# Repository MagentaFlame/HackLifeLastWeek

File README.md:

Helloooo this is last week of design for hack life, and I'm doing a split keyboard!
Ever since I learned about being able to do one from Hack club, I've been looking for opportunities to. Now that I got one, hopefully I have enough free time to do it. I feel bad about not doing my college apps and my tons of hw...

Schematic!

The labels are kind of scuffed. I pretty much made a matrix of 25 keys, using as much as possible, and customized where the pins pointed to so it was easier to route on the pcb. 

PCB!

This took so so long. So currently, most of the letter keys are assembled in a staggered format, similar to a regular keyboard. This is to retain muscle memory for typing and gaming. The ctrl button the left side and space button on the right are still within the 5x5 matrix for the pins, but are one row down for muscle memory.

Code!

I had to create a custom keyboard module using zmk. I learned and implemented making new shields for each side, setting ids, doing soft-off power management, and doing keymaps. In the keymaps, mod-morphs, macros, hold-taps, and regular kps were used to give more complex, unique functionalities. This way, it isn't one/two outputs for each press, but potentially 3/4 depending on which layer (gaming or default) is toggled and the combination of keys pressed. 
I also made sure to write my configs down for future reference and to make sure I don't forget over the few days I do this project.

CAD!

Okay so I wanted the two sides to be vastly different - one hard and modern, while the other more flowy. But, the flowy side isn't to my liking as much as the geometric side b/c I didn't make it flowy enough lol. Anyways, hopefully the color combos will be good. I add only engravings this time, b/c extra details like changing wall geometry and embossing will take time I don't have unfortunately.
The pictures show the colors for the cases. The keycaps for the purple side will be gray and more jagged than the red keycaps on the orange side.
https://cad.onshape.com/documents/0349a2efe14c8a7447e63041/w/2e8c132947c776d3aa7bf3c9/e/34fe7648d6cb8c38b9c40c14 

BOM!

| Item | Qty |	Supplier | Cost/item |	Total Cost |	link |
| ---- | --- |  -------- | --------- | ----------- | ----- |
|Lipo batteries 2pc	|1|	Aliexpress|	$6.39|	$6.39|	https://www.aliexpress.us/item/3256813194775738.html?spm=a2g0o.cart.0.0.3b7f38dawnxLUB&mp=1&pdp_npi=6%40dis%21USD%21USD+17.06%21USD+6.39%21%21USD+5.38%21%21%21%4021032c8d17939128056472314e101d%2112000060946039596%21ct%21US%218326311333%21%212%210%21&_gl=1*vcxzl1*_gcl_aw*R0NMLjE3OTM4MjU2ODEuQ2p3S0NBanc5UHZXQmhBeEVpd0FkZHpZeWZ0RWJBRHV0MFp1THBmbjhScHQ0RHNHWnd5N2dsNnZkbnFycTN0ZDZIZUFDYklOaW9WZ2dCb0MxZ3NRQXZEX0J3RQ..*_gcl_dc*R0NMLjE3OTM4MjU2ODEuQ2p3S0NBanc5UHZXQmhBeEVpd0FkZHpZeWZ0RWJBRHV0MFp1THBmbjhScHQ0RHNHWnd5N2dsNnZkbnFycTN0ZDZIZUFDYklOaW9WZ2dCb0MxZ3NRQXZEX0J3RQ..*_gcl_au*MTczOTE2ODQ4MC4xNzkyMTg4MzIz*_ga*MTU3NzE5MTE5Ny4xNzkzMjI3OTEx*_ga_VED1YSGNC7*czE3OTM5MDgwNzIkbzckZzEkdDE3OTM5MTI4MjQkajQwJGwwJGgw&gatewayAdapt=glo2usa |
|Hot swap sockets|	1|Aliexpress|	$5.43|	$5.43|	https://www.aliexpress.us/item/2251832764937566.html?spm=a2g0o.cart.0.0.3b7f38da0QjVnx&mp=1&pdp_npi=6%40dis%21USD%21USD+6.06%21USD+5.43%21%21USD+4.65%21%21%21%4021030f4a17939133456333682e0f45%2112000036652544705%21ct%21US%218326311333%21%211%210%21&_gl=1*f2u40p*_gcl_aw*R0NMLjE3OTM4MjU2ODEuQ2p3S0NBanc5UHZXQmhBeEVpd0FkZHpZeWZ0RWJBRHV0MFp1THBmbjhScHQ0RHNHWnd5N2dsNnZkbnFycTN0ZDZIZUFDYklOaW9WZ2dCb0MxZ3NRQXZEX0J3RQ..*_gcl_dc*R0NMLjE3OTM4MjU2ODEuQ2p3S0NBanc5UHZXQmhBeEVpd0FkZHpZeWZ0RWJBRHV0MFp1THBmbjhScHQ0RHNHWnd5N2dsNnZkbnFycTN0ZDZIZUFDYklOaW9WZ2dCb0MxZ3NRQXZEX0J3RQ..*_gcl_au*MTczOTE2ODQ4MC4xNzkyMTg4MzIz*_ga*MTU3NzE5MTE5Ny4xNzkzMjI3OTEx*_ga_VED1YSGNC7*czE3OTM5MDgwNzIkbzckZzEkdDE3OTM5MTMzNDckajU4JGwwJGgw&gatewayAdapt=glo2usa|
|2M Resistor (100pc)|	1|	Aliexpress|	$1.86	|$1.86	|https://www.aliexpress.us/item/3256806797741926.html?spm=a2g0o.cart.0.0.3b7f38da0QjVnx&mp=1&pdp_npi=6%40dis%21USD%21USD%202.82%21USD%201.86%21%21USD%201.59%21%21%21%4021030f4a17939133456333682e0f45%2112000038943042510%21ct%21US%218326311333%21%211%210%21&_gl=1*hvxv5j*_gcl_aw*R0NMLjE3OTM4MjU2ODEuQ2p3S0NBanc5UHZXQmhBeEVpd0FkZHpZeWZ0RWJBRHV0MFp1THBmbjhScHQ0RHNHWnd5N2dsNnZkbnFycTN0ZDZIZUFDYklOaW9WZ2dCb0MxZ3NRQXZEX0J3RQ..*_gcl_dc*R0NMLjE3OTM4MjU2ODEuQ2p3S0NBanc5UHZXQmhBeEVpd0FkZHpZeWZ0RWJBRHV0MFp1THBmbjhScHQ0RHNHWnd5N2dsNnZkbnFycTN0ZDZIZUFDYklOaW9WZ2dCb0MxZ3NRQXZEX0J3RQ..*_gcl_au*MTczOTE2ODQ4MC4xNzkyMTg4MzIz*_ga*MTU3NzE5MTE5Ny4xNzkzMjI3OTEx*_ga_VED1YSGNC7*czE3OTM5MDgwNzIkbzckZzEkdDE3OTM5MTMzNjIkajQzJGwwJGgw&gatewayAdapt=glo2usa&_randl_shipto=US|
|806k Resistor (100pc)	|1|	Aliexpress|	$2.28|	$2.28|	https://www.aliexpress.us/item/3256804997915352.html?spm=a2g0o.cart.0.0.3b7f38da0QjVnx&mp=1&pdp_npi=6%40dis%21USD%21USD+2.28%21USD+2.28%21%21USD+1.95%21%21%21%4021030f4a17939133456333682e0f45%2112000032017018120%21ct%21US%218326311333%21%211%210%21&_gl=1*10htlic*_gcl_aw*R0NMLjE3OTM4MjU2ODEuQ2p3S0NBanc5UHZXQmhBeEVpd0FkZHpZeWZ0RWJBRHV0MFp1THBmbjhScHQ0RHNHWnd5N2dsNnZkbnFycTN0ZDZIZUFDYklOaW9WZ2dCb0MxZ3NRQXZEX0J3RQ..*_gcl_dc*R0NMLjE3OTM4MjU2ODEuQ2p3S0NBanc5UHZXQmhBeEVpd0FkZHpZeWZ0RWJBRHV0MFp1THBmbjhScHQ0RHNHWnd5N2dsNnZkbnFycTN0ZDZIZUFDYklOaW9WZ2dCb0MxZ3NRQXZEX0J3RQ..*_gcl_au*MTczOTE2ODQ4MC4xNzkyMTg4MzIz*_ga*MTU3NzE5MTE5Ny4xNzkzMjI3OTEx*_ga_VED1YSGNC7*czE3OTM5MDgwNzIkbzckZzEkdDE3OTM5MTM0NTEkajU4JGwwJGgw&gatewayAdapt=glo2usa|
|1N5819 diode (100pc)|	1|	Aliexpress|	$2.52|	$2.52|	https://aliexpress.us/item/3256811563559109.html?spm=a2g0o.cart.0.0.3b7f38da0QjVnx&mp=1&pdp_npi=6%40dis%21USD%21USD%202.71%21USD%202.52%21%21USD%202.16%21%21%21%4021030f4a17939133456333682e0f45%2112000056430529218%21ct%21US%218326311333%21%211%210%21&_gl=1*p639if*_gcl_aw*R0NMLjE3OTM4MjU2ODEuQ2p3S0NBanc5UHZXQmhBeEVpd0FkZHpZeWZ0RWJBRHV0MFp1THBmbjhScHQ0RHNHWnd5N2dsNnZkbnFycTN0ZDZIZUFDYklOaW9WZ2dCb0MxZ3NRQXZEX0J3RQ..*_gcl_dc*R0NMLjE3OTM4MjU2ODEuQ2p3S0NBanc5UHZXQmhBeEVpd0FkZHpZeWZ0RWJBRHV0MFp1THBmbjhScHQ0RHNHWnd5N2dsNnZkbnFycTN0ZDZIZUFDYklOaW9WZ2dCb0MxZ3NRQXZEX0J3RQ..*_gcl_au*MTczOTE2ODQ4MC4xNzkyMTg4MzIz*_ga*MTU3NzE5MTE5Ny4xNzkzMjI3OTEx*_ga_VED1YSGNC7*czE3OTM5MDgwNzIkbzckZzEkdDE3OTM5MTM1MDckajIkbDAkaDA.&gatewayAdapt=glo2usa&_randl_shipto=US|
|Outemu Silent Lemon v3 Switch (50pc)|	1|	Aliexpress|	$9.49|	$9.49|	https://www.aliexpress.us/item/3256806837508228.html?spm=a2g0o.cart.0.0.3b7f38da0QjVnx&mp=1&pdp_npi=6%40dis%21USD%21USD+10.66%21USD+9.49%21%21USD+8.12%21%21%21%4021030f4a17939133456333682e0f45%2112000039119542623%21ct%21US%218326311333%21%211%210%21&_gl=1*xwxxe5*_gcl_aw*R0NMLjE3OTM4MjU2ODEuQ2p3S0NBanc5UHZXQmhBeEVpd0FkZHpZeWZ0RWJBRHV0MFp1THBmbjhScHQ0RHNHWnd5N2dsNnZkbnFycTN0ZDZIZUFDYklOaW9WZ2dCb0MxZ3NRQXZEX0J3RQ..*_gcl_dc*R0NMLjE3OTM4MjU2ODEuQ2p3S0NBanc5UHZXQmhBeEVpd0FkZHpZeWZ0RWJBRHV0MFp1THBmbjhScHQ0RHNHWnd5N2dsNnZkbnFycTN0ZDZIZUFDYklOaW9WZ2dCb0MxZ3NRQXZEX0J3RQ..*_gcl_au*MTczOTE2ODQ4MC4xNzkyMTg4MzIz*_ga*MTU3NzE5MTE5Ny4xNzkzMjI3OTEx*_ga_VED1YSGNC7*czE3OTM5MDgwNzIkbzckZzEkdDE3OTM5MTM1MTYkajYwJGwwJGgw&gatewayAdapt=glo2usa|
|XIAO nRF52840|	2|	Seeed Studio|	$9.99|	$19.98	|https://www.seeedstudio.com/Seeed-XIAO-BLE-nRF52840-p-5201.html?srsltid=AYCX9vLI_KwrC99kiBzCmS7TrKkTqYekleFYA7gHI7japWQgcSidnN09|
|Custom pcb|	1|	JLCPCB|	$16.95|	$16.95|	https://cart.jlcpcb.com/shopcart/cart/|
|M2 screws 6mm (200pc)|	1|	Aliexpress|	$2.43|	$2.43|	https://aliexpress.us/item/3256808326585307.html?spm=a2g0o.cart.0.0.3a3d38daXM6BNr&mp=1&pdp_npi=6%40dis%21USD%21USD%203.00%21USD%202.43%21%21USD%202.10%21%21%21%40210303cd17939214157478397e0ddd%2112000045495593376%21ct%21US%218326311333%21%211%210%21&_gl=1*i5d2vl*_gcl_aw*R0NMLjE3OTM4MjU2ODEuQ2p3S0NBanc5UHZXQmhBeEVpd0FkZHpZeWZ0RWJBRHV0MFp1THBmbjhScHQ0RHNHWnd5N2dsNnZkbnFycTN0ZDZIZUFDYklOaW9WZ2dCb0MxZ3NRQXZEX0J3RQ..*_gcl_dc*R0NMLjE3OTM4MjU2ODEuQ2p3S0NBanc5UHZXQmhBeEVpd0FkZHpZeWZ0RWJBRHV0MFp1THBmbjhScHQ0RHNHWnd5N2dsNnZkbnFycTN0ZDZIZUFDYklOaW9WZ2dCb0MxZ3NRQXZEX0J3RQ..*_gcl_au*MTczOTE2ODQ4MC4xNzkyMTg4MzIz*_ga*MTU3NzE5MTE5Ny4xNzkzMjI3OTEx*_ga_VED1YSGNC7*czE3OTM5MjEwODgkbzgkZzEkdDE3OTM5MjE0MTYkajU0JGwwJGgw&gatewayAdapt=glo2usa&_randl_shipto=US|
|Estimated total shipping|	1|			$11.10|

Only after making the hardware did I realized just how much it costs, even with Aliexpress and the 11.11 deals (hopefully I can get this approved by then). The microcontrollers and custom pcb cost the most, but that is to be expected. Just once added together, it accumulated to a lot. I think I can get enough hours for the tier 3 funding though.

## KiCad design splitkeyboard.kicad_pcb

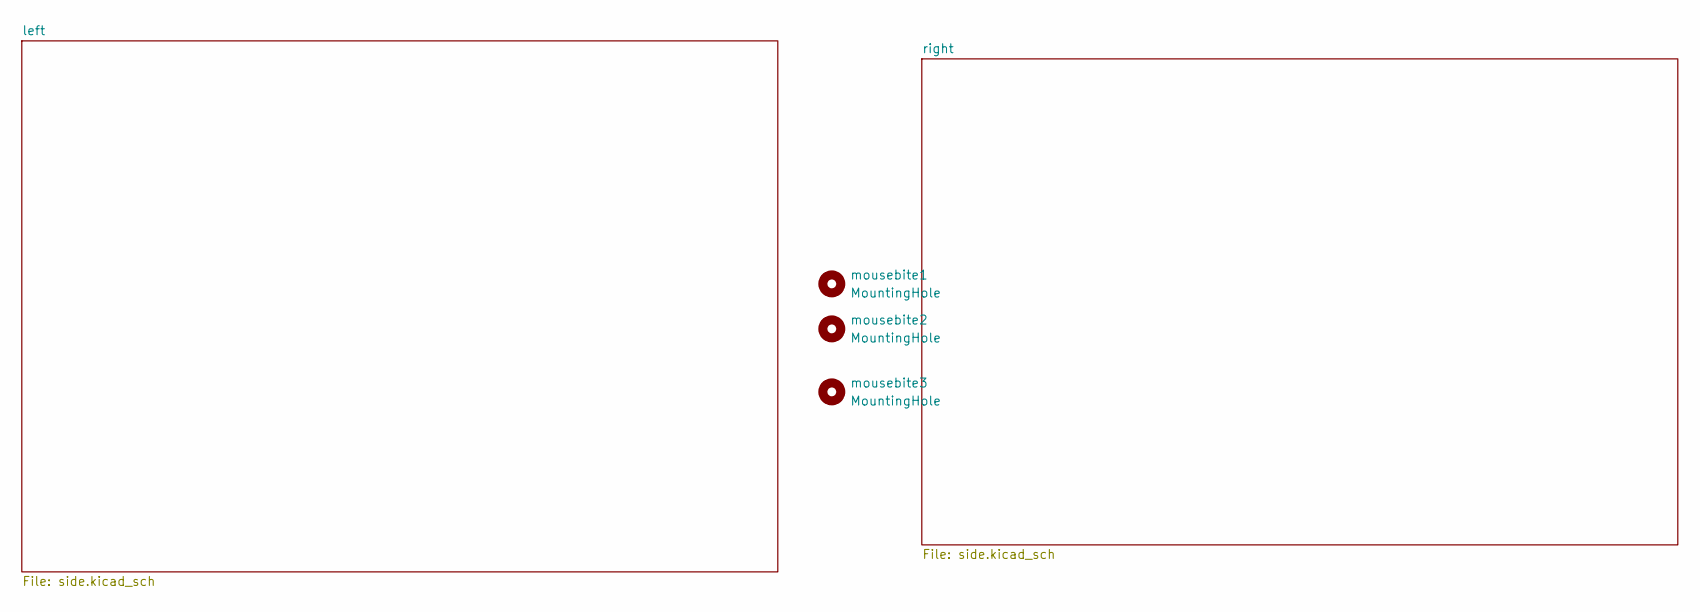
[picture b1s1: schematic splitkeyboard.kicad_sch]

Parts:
mousebite1, mousebite2, mousebite3: MountingHole; mouse-bite-5mm-slot

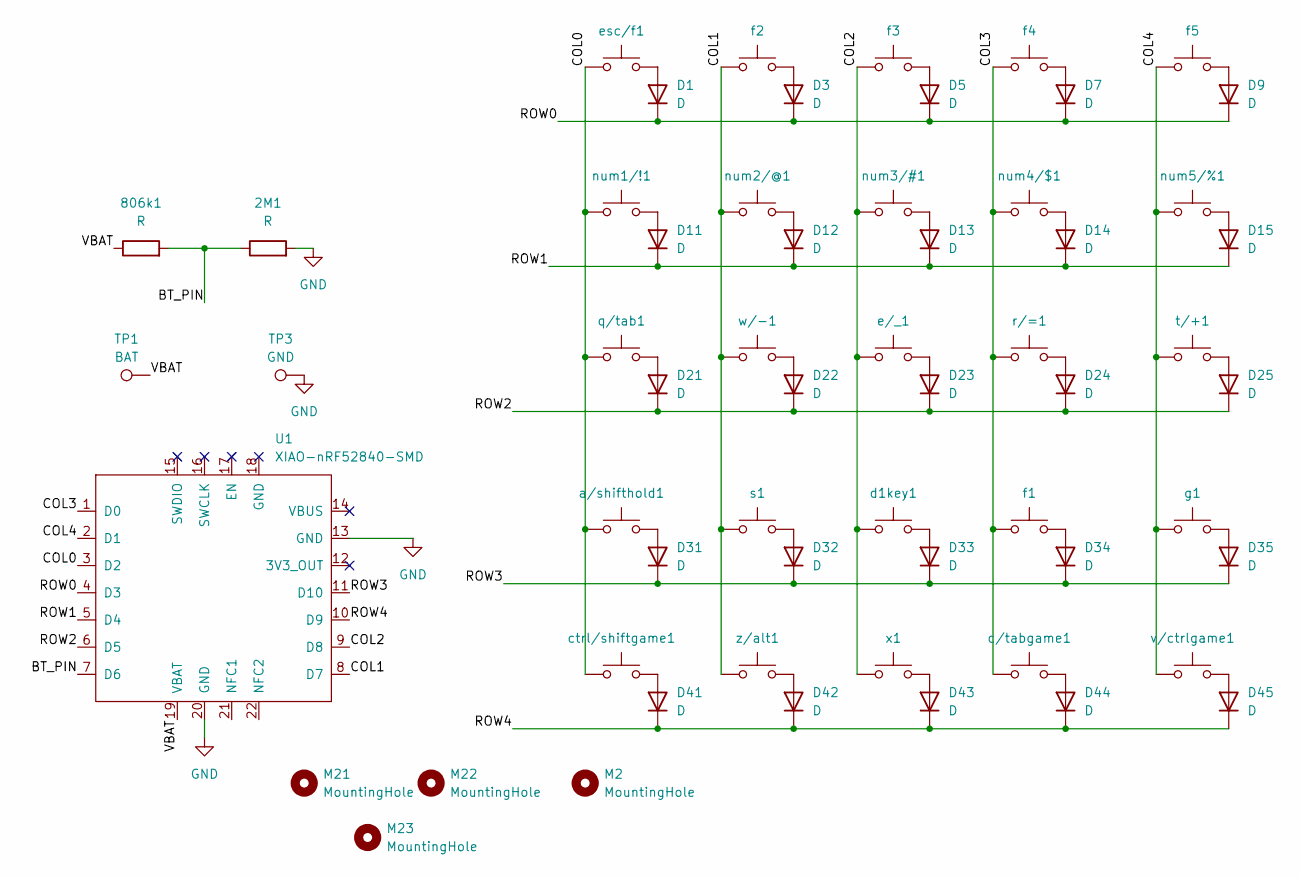
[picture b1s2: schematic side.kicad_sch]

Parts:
2M1, 806k1: R; R_0805_2012Metric
D1, D3, D5, D7, D9, D11, D12, D13, D14, D15, D21, D22, D23, D24, D25, D31, D32, D33, D34, D35, D41, D42, D43, D44, D45: D; D_SOD-123
M2, M21, M22, M23: MountingHole; MountingHole_2.2mm_M2
TP1: BAT; TestPoint_Pad_D2.0mm
TP3: GND; TestPoint_Pad_D2.0mm
U1: XIAO-nRF52840-SMD; modified-XIAO-nRF52840-SMD
a/shifthold1: SW_Push; SW_MX_HS_CPG151101S11_1u
c/tabgame1: SW_Push; SW_MX_HS_CPG151101S11_1u
ctrl/shiftgame1: SW_Push; SW_MX_HS_CPG151101S11_1u
d1key1: SW_Push; SW_MX_HS_CPG151101S11_1u
e/_1: SW_Push; SW_MX_HS_CPG151101S11_1u
esc/f1: SW_Push; SW_MX_HS_CPG151101S11_1u
f1, f2, f3, f4, f5: SW_Push; SW_MX_HS_CPG151101S11_1u
g1: SW_Push; SW_MX_HS_CPG151101S11_1u
num1/!1, num2/@1, num3/#1, num4/$1, num5/%1: SW_Push; SW_MX_HS_CPG151101S11_1u
q/tab1: SW_Push; SW_MX_HS_CPG151101S11_1u
r/=1: SW_Push; SW_MX_HS_CPG151101S11_1u
s1: SW_Push; SW_MX_HS_CPG151101S11_1u
t/+1: SW_Push; SW_MX_HS_CPG151101S11_1u
v/ctrlgame1: SW_Push; SW_MX_HS_CPG151101S11_1u
w/-1: SW_Push; SW_MX_HS_CPG151101S11_1u
x1: SW_Push; SW_MX_HS_CPG151101S11_1u
z/alt1: SW_Push; SW_MX_HS_CPG151101S11_1u

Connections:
/left/BT_PIN: 2M1.1, 806k1.2, U1.7 (D6)
/left/COL0: U1.3 (D2), a/shifthold1.1, ctrl/shiftgame1.1, esc/f1.1, num1/!1.1, q/tab1.1
/left/COL1: U1.8 (D7), f2.1, num2/@1.1, s1.1, w/-1.1, z/alt1.1
/left/COL2: U1.9 (D8), d1key1.1, e/_1.1, f3.1, num3/#1.1, x1.1
/left/COL3: U1.1 (D0), c/tabgame1.1, f1.1, f4.1, num4/$1.1, r/=1.1
/left/COL4: U1.2 (D1), f5.1, g1.1, num5/%1.1, t/+1.1, v/ctrlgame1.1
/left/ROW0: D1.1 (K), D3.1 (K), D5.1 (K), D7.1 (K), D9.1 (K), U1.4 (D3)
/left/ROW1: D11.1 (K), D12.1 (K), D13.1 (K), D14.1 (K), D15.1 (K), U1.5 (D4)
/left/ROW2: D21.1 (K), D22.1 (K), D23.1 (K), D24.1 (K), D25.1 (K), U1.6 (D5)
/left/ROW3: D31.1 (K), D32.1 (K), D33.1 (K), D34.1 (K), D35.1 (K), U1.11 (D10)
/left/ROW4: D41.1 (K), D42.1 (K), D43.1 (K), D44.1 (K), D45.1 (K), U1.10 (D9)
/left/VBAT: 806k1.1, TP1.1 (1_1), U1.19 (VBAT)
GND: 2M1.2, TP3.1 (1_1), U1.13 (GND), U1.20 (GND); also elsewhere on the board
unnamed: D1.2 (A), esc/f1.2
unnamed: D3.2 (A), f2.2
unnamed: D5.2 (A), f3.2
unnamed: D7.2 (A), f4.2
unnamed: D9.2 (A), f5.2
unnamed: D11.2 (A), num1/!1.2
unnamed: D12.2 (A), num2/@1.2
unnamed: D13.2 (A), num3/#1.2
unnamed: D14.2 (A), num4/$1.2
unnamed: D15.2 (A), num5/%1.2
unnamed: D21.2 (A), q/tab1.2
unnamed: D22.2 (A), w/-1.2
unnamed: D23.2 (A), e/_1.2
unnamed: D24.2 (A), r/=1.2
unnamed: D25.2 (A), t/+1.2
unnamed: D31.2 (A), a/shifthold1.2
unnamed: D32.2 (A), s1.2
unnamed: D33.2 (A), d1key1.2
unnamed: D34.2 (A), f1.2
unnamed: D35.2 (A), g1.2
unnamed: D41.2 (A), ctrl/shiftgame1.2
unnamed: D42.2 (A), z/alt1.2
unnamed: D43.2 (A), x1.2
unnamed: D44.2 (A), c/tabgame1.2
unnamed: D45.2 (A), v/ctrlgame1.2

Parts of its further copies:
2M2, 806k2: R; R_0805_2012Metric
//rightarrow/downarrow1: SW_Push; SW_MX_HS_CPG151101S11_1u
D2, D4, D6, D8, D10, D16, D17, D18, D19, D20, D26, D27, D28, D29, D30, D36, D37, D38, D39, D40, D46, D47, D48, D49, D50: D; D_SOD-123
H2, H4, H6, H8: MountingHole; MountingHole_2.2mm_M2
TP2: BAT; TestPoint_Pad_D2.0mm
TP4: GND; TestPoint_Pad_D2.0mm
U2: XIAO-nRF52840-SMD; modified-XIAO-nRF52840-SMD
b/,1: SW_Push; SW_MX_HS_CPG151101S11_1u
backspace/delete1: SW_Push; SW_MX_HS_CPG151101S11_1u
enter/1: SW_Push; SW_MX_HS_CPG151101S11_1u
f6, f7, f8, f9: SW_Push; SW_MX_HS_CPG151101S11_1u
h/:1: SW_Push; SW_MX_HS_CPG151101S11_1u
i/}1: SW_Push; SW_MX_HS_CPG151101S11_1u
j/;1: SW_Push; SW_MX_HS_CPG151101S11_1u
k/"1: SW_Push; SW_MX_HS_CPG151101S11_1u
l/'1: SW_Push; SW_MX_HS_CPG151101S11_1u
m/leftarrow/uparrow1: SW_Push; SW_MX_HS_CPG151101S11_1u
n/.1: SW_Push; SW_MX_HS_CPG151101S11_1u
num0/)1, num6/^1, num7/&1, num8/*1, num9/(1: SW_Push; SW_MX_HS_CPG151101S11_1u
o/[1: SW_Push; SW_MX_HS_CPG151101S11_1u
p/]1: SW_Push; SW_MX_HS_CPG151101S11_1u
space/>1: SW_Push; SW_MX_HS_CPG151101S11_1u
u/{1: SW_Push; SW_MX_HS_CPG151101S11_1u
y/<1: SW_Push; SW_MX_HS_CPG151101S11_1u

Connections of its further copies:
/right/BT_PIN: 2M2.1, 806k2.2, U2.7 (D6)
/right/COL0: U2.3 (D2), f6.1, h/:1.1, num6/^1.1, space/>1.1, y/<1.1
/right/COL1: U2.8 (D7), b/,1.1, f7.1, j/;1.1, num7/&1.1, u/{1.1
/right/COL2: U2.9 (D8), f8.1, i/}1.1, k/"1.1, n/.1.1, num8/*1.1
/right/COL3: U2.1 (D0), f9.1, l/'1.1, m/leftarrow/uparrow1.1, num9/(1.1, o/[1.1
/right/COL4: //rightarrow/downarrow1.1, U2.2 (D1), backspace/delete1.1, enter/1.1, num0/)1.1, p/]1.1
/right/ROW0: D2.1 (K), D4.1 (K), D6.1 (K), D8.1 (K), D10.1 (K), U2.4 (D3)
/right/ROW1: D16.1 (K), D17.1 (K), D18.1 (K), D19.1 (K), D20.1 (K), U2.5 (D4)
/right/ROW2: D26.1 (K), D27.1 (K), D28.1 (K), D29.1 (K), D30.1 (K), U2.6 (D5)
/right/ROW3: D36.1 (K), D37.1 (K), D38.1 (K), D39.1 (K), D40.1 (K), U2.11 (D10)
/right/ROW4: D46.1 (K), D47.1 (K), D48.1 (K), D49.1 (K), D50.1 (K), U2.10 (D9)
/right/VBAT: 806k2.1, TP2.1 (1_1), U2.19 (VBAT)
GND: 2M2.2, TP4.1 (1_1), U2.13 (GND), U2.20 (GND); also elsewhere on the board
unnamed: D2.2 (A), f6.2
unnamed: D4.2 (A), f7.2
unnamed: D6.2 (A), f8.2
unnamed: D8.2 (A), f9.2
unnamed: D10.2 (A), backspace/delete1.2
unnamed: D16.2 (A), num6/^1.2
unnamed: D17.2 (A), num7/&1.2
unnamed: D18.2 (A), num8/*1.2
unnamed: D19.2 (A), num9/(1.2
unnamed: D20.2 (A), num0/)1.2
unnamed: D26.2 (A), y/<1.2
unnamed: D27.2 (A), u/{1.2
unnamed: D28.2 (A), i/}1.2
unnamed: D29.2 (A), o/[1.2
unnamed: D30.2 (A), p/]1.2
unnamed: D36.2 (A), h/:1.2
unnamed: D37.2 (A), j/;1.2
unnamed: D38.2 (A), k/"1.2
unnamed: D39.2 (A), l/'1.2
unnamed: D40.2 (A), enter/1.2
unnamed: D46.2 (A), space/>1.2
unnamed: D47.2 (A), b/,1.2
unnamed: D48.2 (A), n/.1.2
unnamed: D49.2 (A), m/leftarrow/uparrow1.2
unnamed: //rightarrow/downarrow1.2, D50.2 (A)

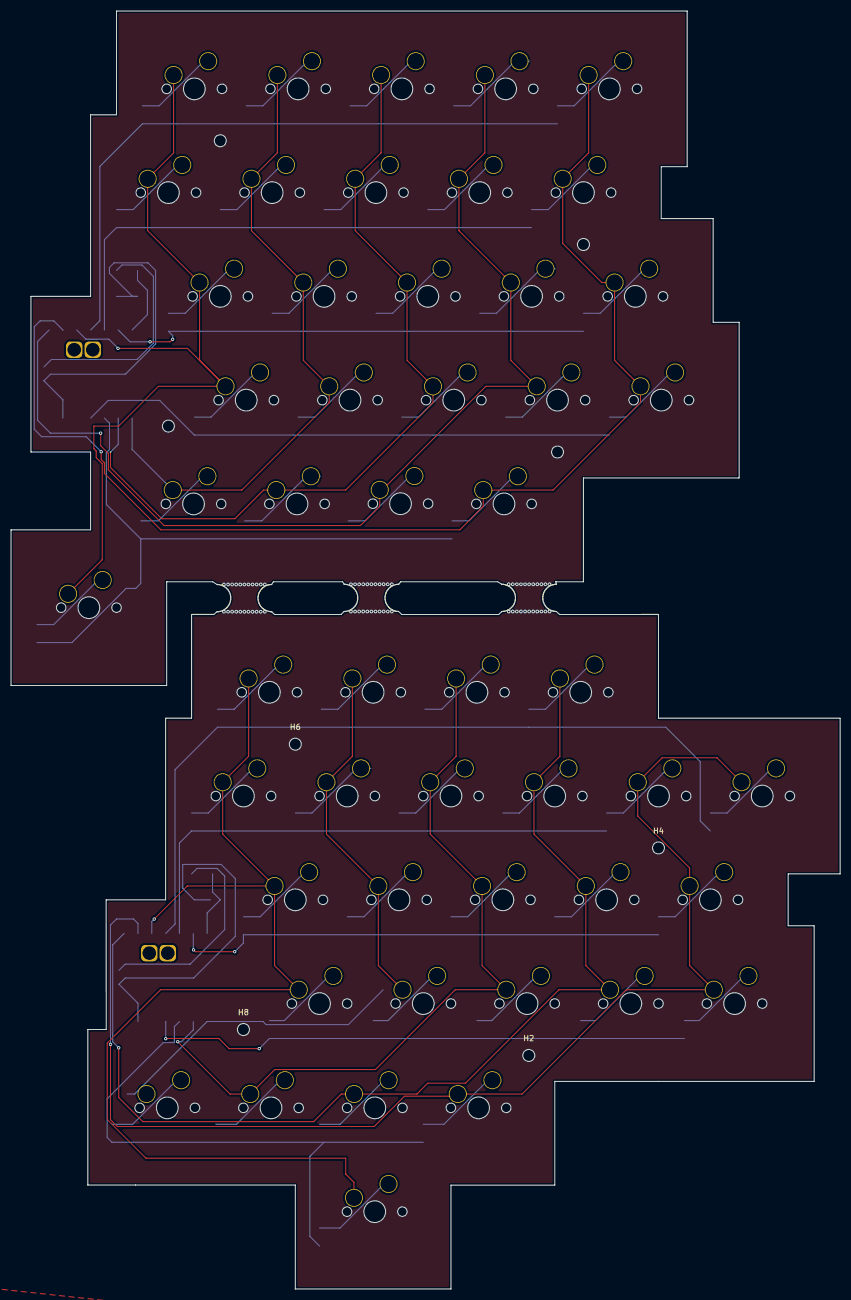
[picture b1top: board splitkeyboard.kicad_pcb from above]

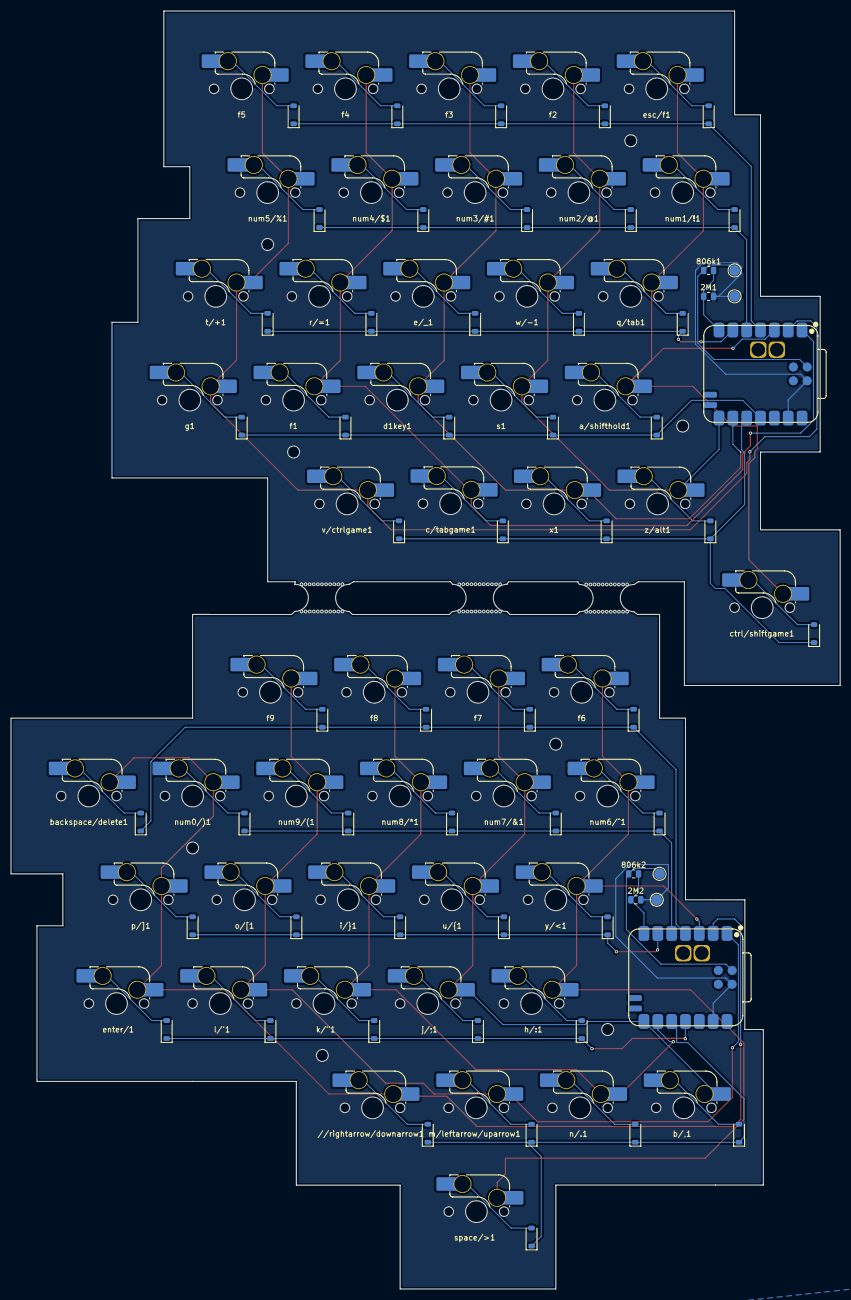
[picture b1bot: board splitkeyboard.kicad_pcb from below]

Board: 2 copper layers, 152.2 x 234.6 mm, 121 parts (110 on the bottom side), 75 nets.
